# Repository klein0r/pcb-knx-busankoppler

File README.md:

# KNX 5WG1117-2AB12 Adapter PCB

[Gerber-Files](https://github.com/klein0r/pcb-knx-busankoppler/releases)

## Preview

## License

The MIT License (MIT)

Copyright (c) 2026 Matthias Kleine <info@haus-automatisierung.com>

Permission is hereby granted, free of charge, to any person obtaining a copy
of this software and associated documentation files (the "Software"), to deal
in the Software without restriction, including without limitation the rights
to use, copy, modify, merge, publish, distribute, sublicense, and/or sell
copies of the Software, and to permit persons to whom the Software is
furnished to do so, subject to the following conditions:

The above copyright notice and this permission notice shall be included in
all copies or substantial portions of the Software.

THE SOFTWARE IS PROVIDED "AS IS", WITHOUT WARRANTY OF ANY KIND, EXPRESS OR
IMPLIED, INCLUDING BUT NOT LIMITED TO THE WARRANTIES OF MERCHANTABILITY,
FITNESS FOR A PARTICULAR PURPOSE AND NONINFRINGEMENT. IN NO EVENT SHALL THE
AUTHORS OR COPYRIGHT HOLDERS BE LIABLE FOR ANY CLAIM, DAMAGES OR OTHER
LIABILITY, WHETHER IN AN ACTION OF CONTRACT, TORT OR OTHERWISE, ARISING FROM,
OUT OF OR IN CONNECTION WITH THE SOFTWARE OR THE USE OR OTHER DEALINGS IN
THE SOFTWARE.

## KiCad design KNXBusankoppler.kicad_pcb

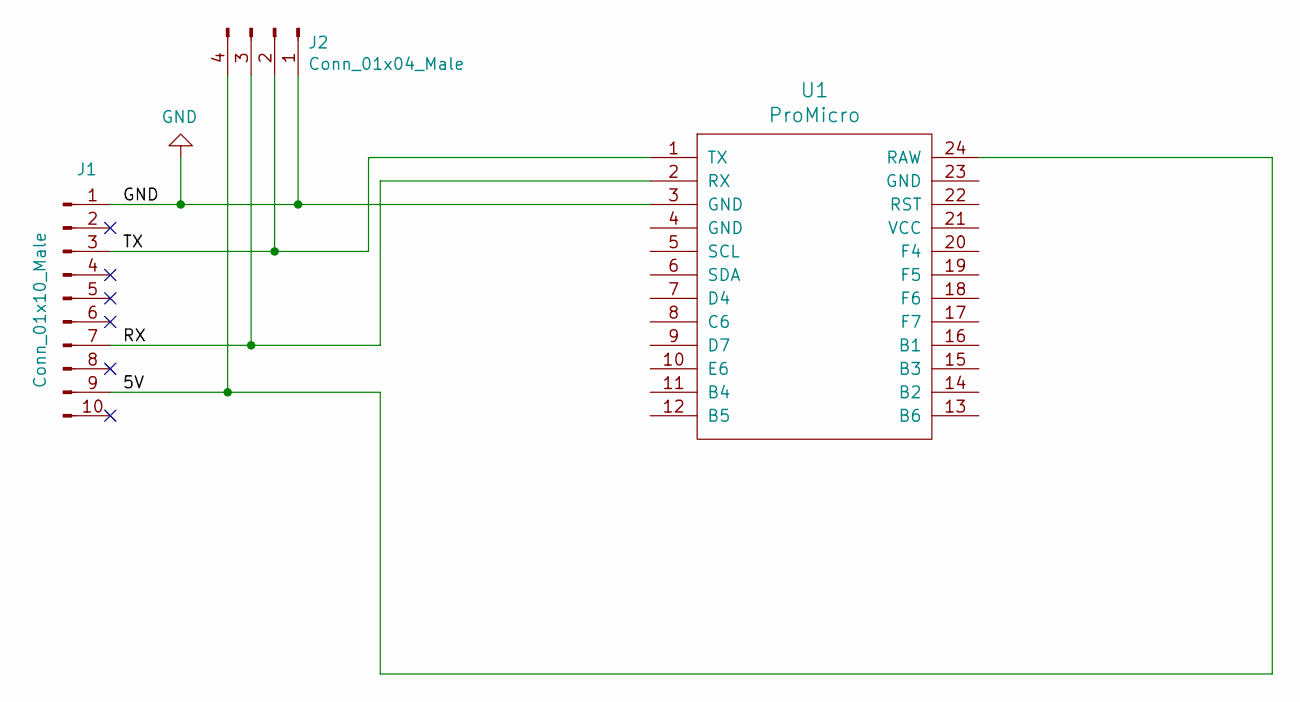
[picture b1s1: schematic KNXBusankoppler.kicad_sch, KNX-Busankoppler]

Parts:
J1: Conn_01x10_Male; PinHeader_2x05_P2.54mm_Vertical
J2: Conn_01x04_Male; PinHeader_1x04_P2.54mm_Vertical
U1: ProMicro; ArduinoProMicro

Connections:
/5V: J1.9, J2.4, U1.24 (RAW)
/RX: J1.7, J2.3, U1.2 (RX)
/TX: J1.3, J2.2, U1.1 (TX)
GND: J1.1, J2.1, U1.3 (GND)

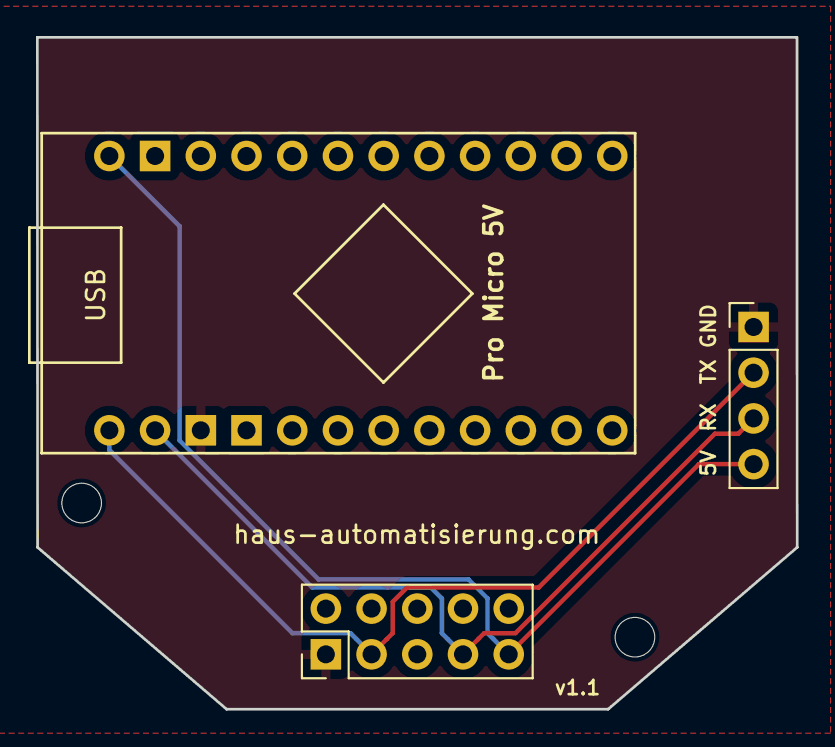
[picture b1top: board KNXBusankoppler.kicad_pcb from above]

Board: 2 copper layers, 42.2 x 37.3 mm, 3 parts (0 on the bottom side), 4 nets.

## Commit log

2019-04-17 Base
2019-04-18 Readme, license and preview
2019-04-28 CO2-Sensor 1.0
2019-04-28 CO2 Preview
2019-04-28 Part List
2019-04-28 Product links
2019-05-11 Changed Footprint
2019-05-17 v1.1
2019-05-17 .bak removed
2022-01-30 Update LICENSE
2022-02-08 Updated to KiCad 6
2024-06-04 Updated preview / year 2024
2026-01-28 Year 2026
